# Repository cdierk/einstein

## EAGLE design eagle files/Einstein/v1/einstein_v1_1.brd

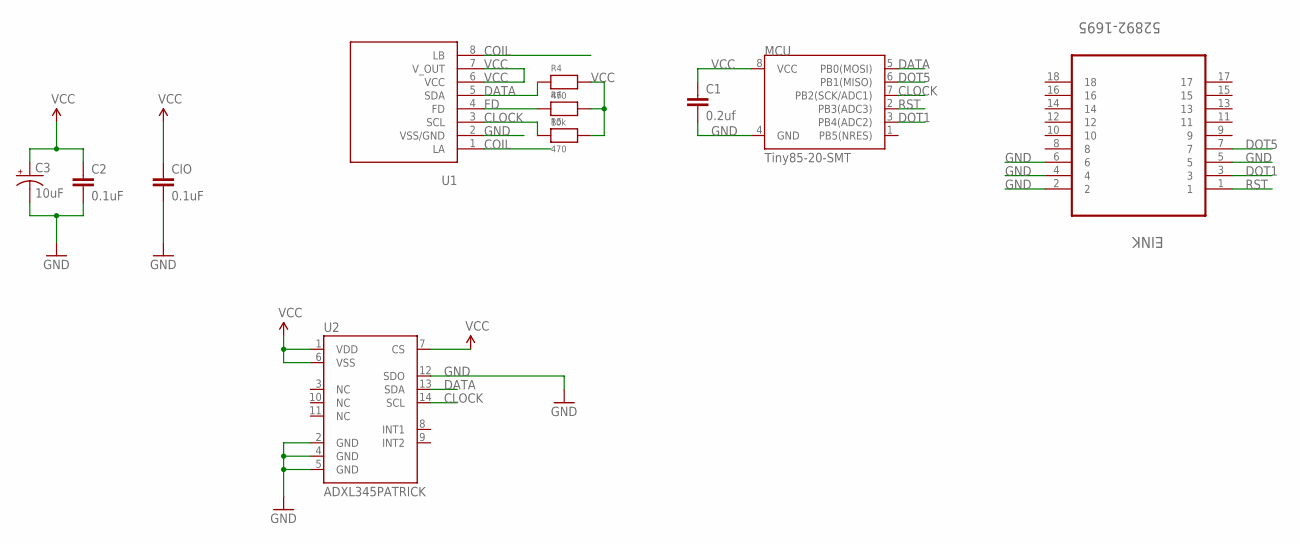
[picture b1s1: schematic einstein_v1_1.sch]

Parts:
C1: 0.2uf; 1206
C2: 0.1uF; 0603-CAP
C3: 10uF; EIA3216
CIO: 0.1uF; 0603-CAP
EINK: 52892-1695; MOLEX_52892-1695
MCU: Tiny85-20-SMT; SO08-EIAJ
R4, R5: 470; 0603
R6: 10k; 0603
U1: NT3H1101
U2: ADXL345PATRICK; LGA14_1:1_PATRICK

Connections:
CLOCK: MCU.7 (PB2(SCK/ADC1)), R5.1, U1.3 (SCL), U2.14 (SCL)
COIL: U1.1 (LA), U1.8 (LB)
DATA: MCU.5 (PB0(MOSI)), R4.1, U1.5 (SDA), U2.13 (SDA)
DOT1: EINK.3, MCU.3 (PB4(ADC2))
DOT5: EINK.7, MCU.6 (PB1(MISO))
FD: R6.1, U1.4 (FD)
GND: C1.2, C2.2, C3.C (-), CIO.2, EINK.2, EINK.4, EINK.5, EINK.6, MCU.4 (GND), U1.2 (VSS/GND), U2.2 (GND), U2.4 (GND), U2.5 (GND), U2.12 (SDO)
RST: EINK.1, MCU.2 (PB3(ADC3))
VCC: C1.1, C2.1, C3.A (+), CIO.1, MCU.8 (VCC), R4.2, R5.2, R6.2, U1.6 (VCC), U1.7 (V_OUT), U2.1 (VDD), U2.6 (VSS), U2.7 (CS)

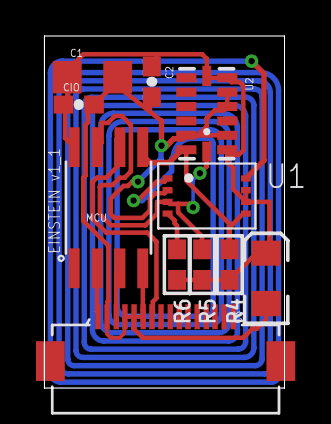
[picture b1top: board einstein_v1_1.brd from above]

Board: 2 copper layers, 13.3 x 19.6 mm, 11 parts (0 on the bottom side), 9 nets.

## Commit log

2017-10-17 basic photocell code
2017-10-17 basic thermistor code
2017-10-17 ATTiny85 read NFC over i2c
2017-11-03 AlterNail V2 eagle files
    NFC tag + ATTiny85 + fpc. Need to replace fpc part with smaller, correct part. Also need to add accelerometer.
2017-11-06 Einstein Board designs
    V1.1
2017-11-07 rather than blinking LED, tap updates eink display
2017-11-07 Added coil for NFC power transfer
    Added coil for NFC power transfer
2017-11-07 Added ADXL
    Added aDXL breakout
2017-11-07 Added Gerber
    Added Gerber
2017-11-08 i2c read/write functionality
2017-11-15 PN532 read from ntag
    able to pull out urls of variable length
2017-11-15 updated Wire library to include TinyWireM
2017-11-15 unedited version of TinyWireM
2017-11-15 unedited version of Wire (included with Arduino IDE)
2017-11-15 updated to pull out URL of variable length
2017-11-15 .
    .
2017-11-18 Dump code
2017-11-21 Adds new URL to nail, updates metadata
2017-11-28 Problem reading & writing to i2c
2017-11-28 Code for image display, link open etc, updated arduino code for local pointer
2017-11-28 updated linkopen_v2 to constantly look for updates
2017-11-28 linkopen_v3 to prevent repeated opening of same links

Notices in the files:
parts and their libraries:
SparkFun-Capacitors: Licensing: Creative Commons ShareAlike 4.0 International - https://creativecommons.org/licenses/by-sa/4.0
microbuilder: This work is placed in the public domain, and may be freely used for commercial and non-commercial work with the following conditions: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
